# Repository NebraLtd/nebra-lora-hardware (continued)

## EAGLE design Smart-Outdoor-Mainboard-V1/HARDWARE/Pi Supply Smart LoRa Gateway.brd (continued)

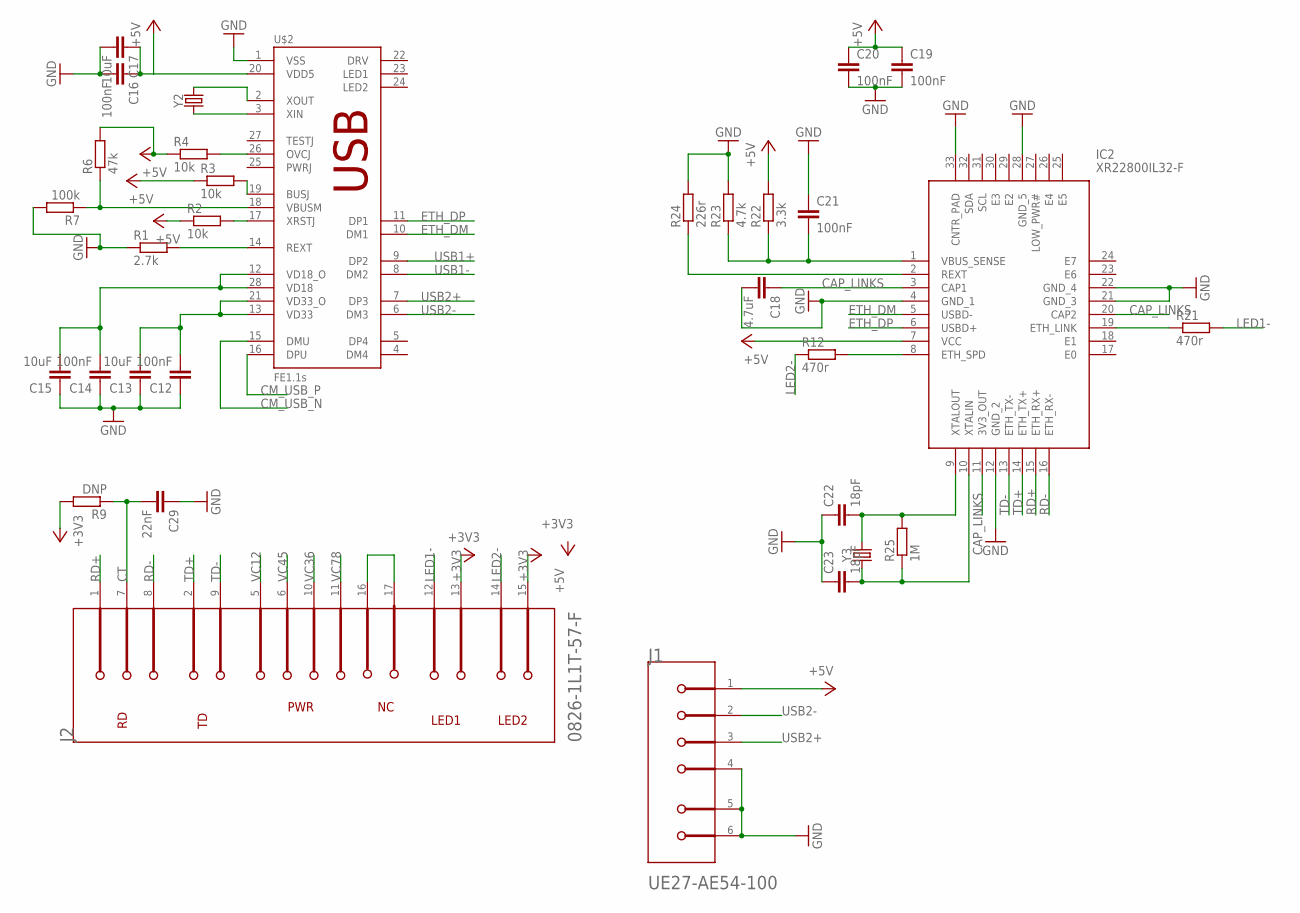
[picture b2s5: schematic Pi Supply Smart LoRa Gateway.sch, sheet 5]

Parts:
C12, C14, C16, C19, C20, C21: 100nF; C0603
C13, C15, C17: 10uF; C0603
C18: 4.7uF; C0603
C22, C23: 18pF; C0603
C29: 22nF; C0603
IC2: XR22800IL32-F; QFN50P500X500X100-33N
J1: AMPHENOL_UE27-AE54-100AMPHENOL_UE27-AE54-100_0_0; AMPHENOL_UE27-AE54-100_0
J2: TRJK1014A8NL; BEL_0826-1L1T-57-F_0
R1: 2.7k; R0603
R2, R3, R4: 10k; R0603
R6: 47k; R0603
R7: 100k; R0603
R9: DNP; R0603
R12, R21: 470r; R0603
R22: 3.3k; R0603
R23: 4.7k; R0603
R24: 226r; R0603
R25: 1M; R0603
U$2: FE1.1S; FE1.1S_SSOP-28
Y2: 12mHZ; HC49UP
Y3: 25Mhz; HC49UP

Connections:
+3V3: J2.13 (2_LED1), J2.15 (LED2_ANODE), R9.2; also elsewhere on the board
+5V: C16.1, C17.1, C19.1, C20.1, IC2.7 (VCC), J1.1, R2.1, R3.1, R4.1, R6.2, R22.2, U$2.20 (VDD5); also elsewhere on the board
CAP_LINKS: C18.1, IC2.3 (CAP1), IC2.11 (3V3_OUT), IC2.20 (CAP2)
CM_USB_N: U$2.15 (DMU); also elsewhere on the board
CM_USB_P: U$2.16 (DPU); also elsewhere on the board
CT: C29.2, J2.7 (CT), R9.1
ETH_DM: IC2.5 (USBD-), U$2.10 (DM1)
ETH_DP: IC2.6 (USBD+), U$2.11 (DP1)
GND: C12.1, C13.1, C14.1, C15.1, C16.2, C17.2, C18.2, C19.2, C20.2, C21.1, C22.1, C23.1, C29.1, IC2.4 (GND_1), IC2.12 (GND_2), IC2.21 (GND_3), IC2.22 (GND_4), IC2.28 (GND_5), IC2.33 (CNTR_PAD), J1.4, J1.5 (MNT_1), J1.6 (MNT_2), R1.1, R7.2, R23.2, R24.2, U$2.1 (VSS); also elsewhere on the board
LED1-: J2.12 (1_LED1), R21.2
LED2-: J2.14 (LED2_CATHODE), R12.1
unnamed: C12.2, C13.2, U$2.13 (VD33), U$2.21 (VD33_O)
unnamed: C14.2, C15.2, U$2.12 (VD18_O), U$2.28 (VD18)
unnamed: R4.2, U$2.26 (OVCJ)
unnamed: R1.2, U$2.14 (REXT)
unnamed: R3.2, U$2.19 (BUSJ)
unnamed: R6.1, R7.1, U$2.18 (VBUSM)
unnamed: R2.2, U$2.17 (XRSTJ)
unnamed: U$2.2 (XOUT), Y2.2
unnamed: U$2.3 (XIN), Y2.1
unnamed: IC2.19 (ETH_LINK), R21.1
unnamed: C23.2, IC2.10 (XTALIN), R25.1, Y3.1
unnamed: C22.2, IC2.9 (XTALOUT), R25.2, Y3.2
unnamed: IC2.8 (ETH_SPD), R12.2
unnamed: J2.16 (1_GND), J2.17 (2_GND)
unnamed: IC2.2 (REXT), R24.1
unnamed: C21.2, IC2.1 (VBUS_SENSE), R22.1, R23.1
RD+: IC2.15 (ETH_RX+), J2.1 (RD+)
RD-: IC2.16 (ETH_RX-), J2.8 (RD-)
TD+: IC2.14 (ETH_TX+), J2.2 (TD+)
TD-: IC2.13 (ETH_TX-), J2.9 (TD-)
USB1+: U$2.9 (DP2); also elsewhere on the board
USB1-: U$2.8 (DM2); also elsewhere on the board
USB2+: J1.3, U$2.7 (DP3)
USB2-: J1.2, U$2.6 (DM3)
VC12: J2.5 (VC12); also elsewhere on the board
VC36: J2.10 (VC36); also elsewhere on the board
VC45: J2.6 (VC45); also elsewhere on the board
VC78: J2.11 (VC78); also elsewhere on the board

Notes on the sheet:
LED2
LED1
PWR
USB

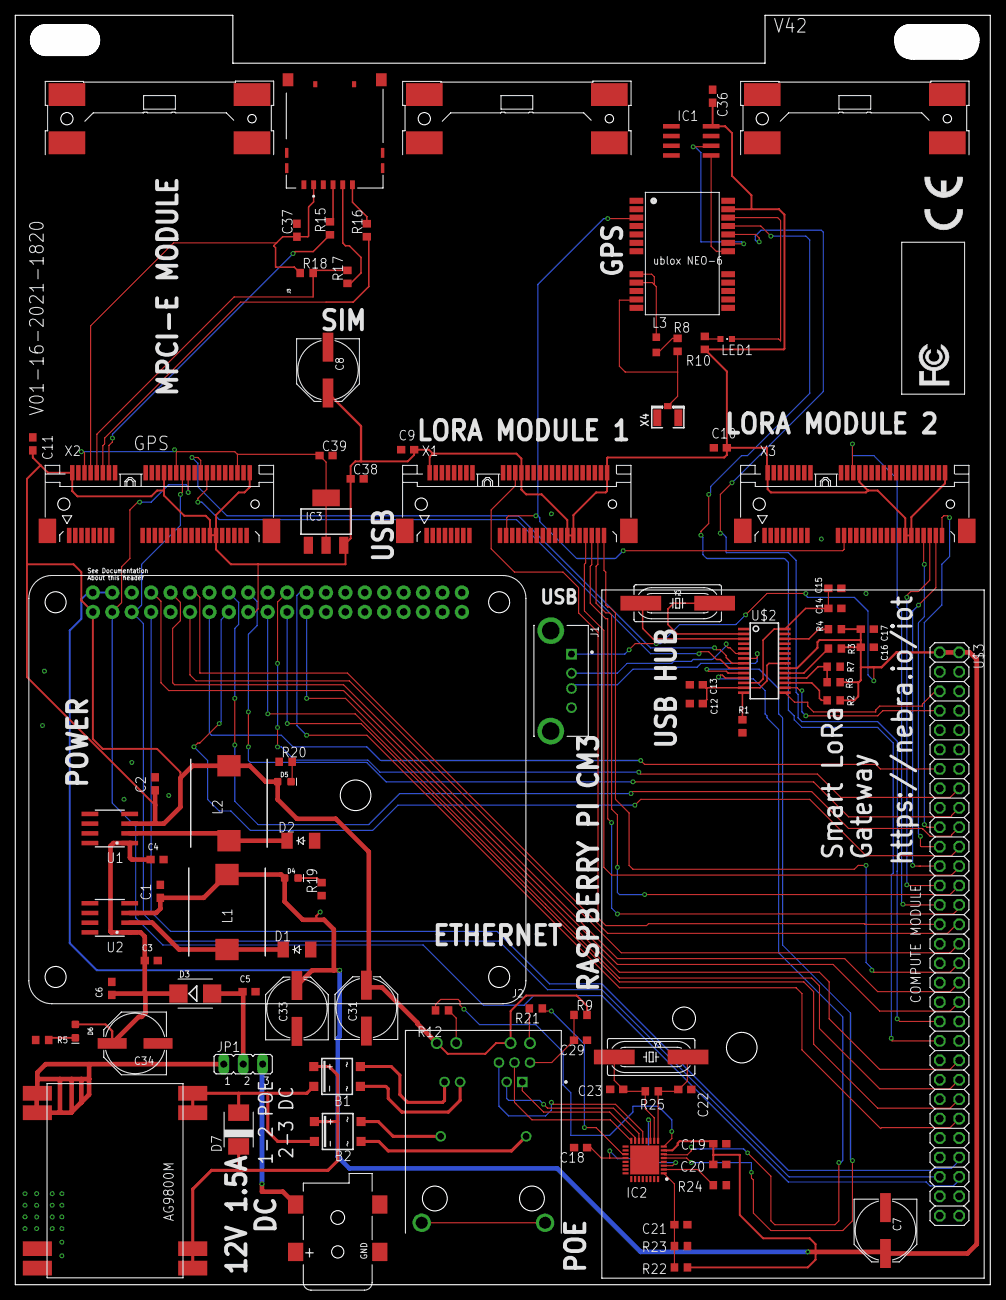
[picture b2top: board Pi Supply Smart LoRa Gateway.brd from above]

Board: 2 copper layers, 123.5 x 162.0 mm, 89 parts (0 on the bottom side), 94 nets.

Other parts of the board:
U$6: FCC_20X8.35MM
U$7: CE_5MM

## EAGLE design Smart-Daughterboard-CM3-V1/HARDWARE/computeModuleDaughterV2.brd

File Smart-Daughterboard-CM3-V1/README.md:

# Nebra Smart Daughterboard CM3
Hardware Files for the CM3 daughterboard for the Nebra Smart Hotspots

This board is used to provide the support circuitry for the CM3/CM3+, and breaks out the GPIO pins along with USB to a 60 Pin Header.

# Daughterboard Connector Pinout
The Daughterboard connector is of our own specification, it allows us in the future to create new daughterboards for other SBCs.

The electrical pinout is as follows:

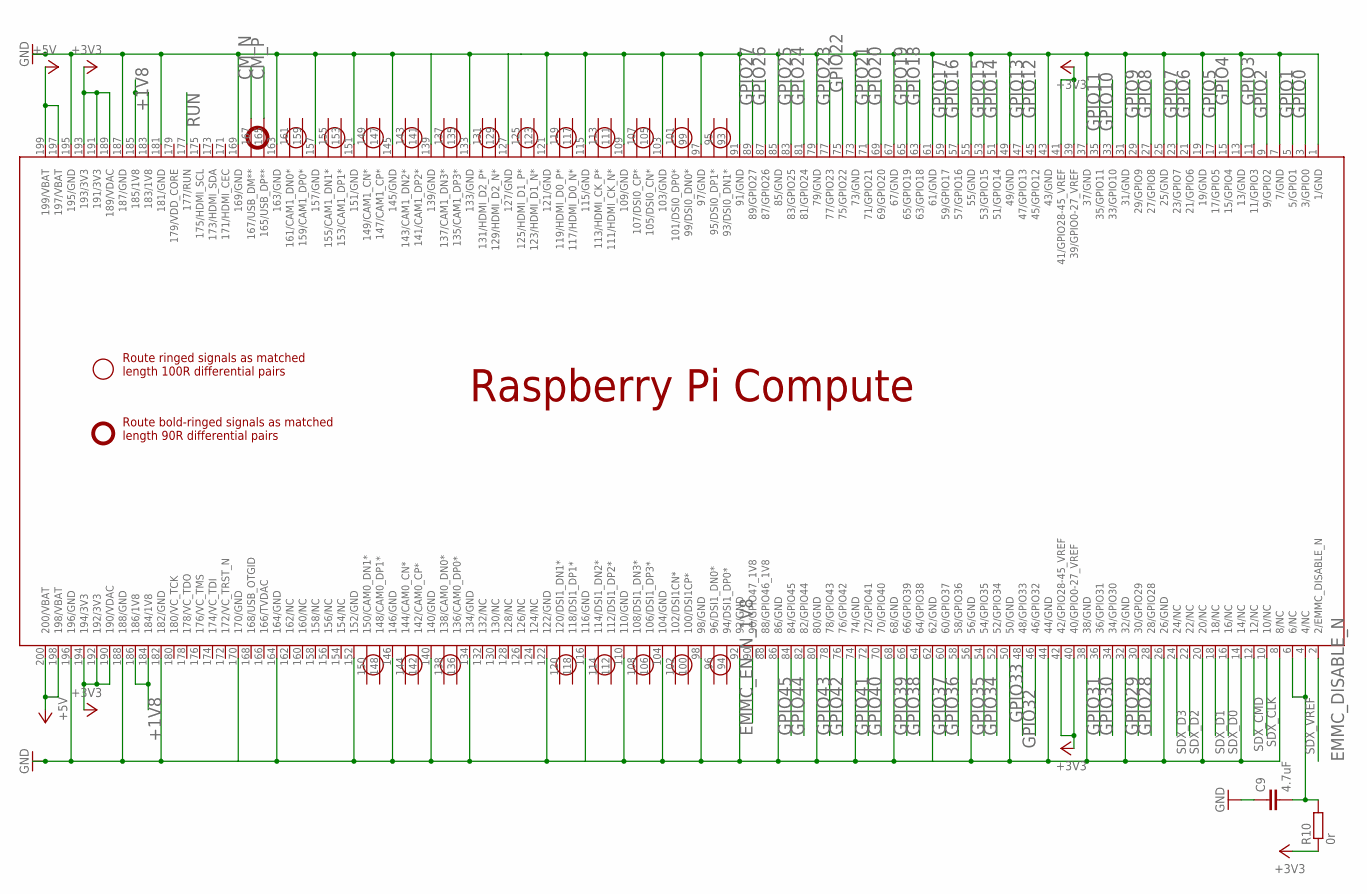
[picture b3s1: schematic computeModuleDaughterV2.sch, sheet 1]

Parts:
C9: 4.7uF; C0603
PCB1: RPI_COMPUTE
R10: 0r; R0603

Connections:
+1V8: PCB1.183 (183/1V8), PCB1.184 (184/1V8), PCB1.185 (185/1V8), PCB1.186 (186/1V8); also elsewhere on the board
+3V3: PCB1.39 (39/GPIO0-27_VREF), PCB1.40 (40/GPIO0-27_VREF), PCB1.41 (41/GPIO28-45_VREF), PCB1.42 (42/GPIO28-45_VREF), PCB1.189 (189/VDAC), PCB1.190 (190/VDAC), PCB1.191 (191/3V3), PCB1.192 (192/3V3), PCB1.193 (193/3V3), PCB1.194 (194/3V3), R10.1; also elsewhere on the board
+5V: PCB1.197 (197/VBAT), PCB1.198 (198/VBAT), PCB1.199 (199/VBAT), PCB1.200 (200/VBAT); also elsewhere on the board
CM_N: PCB1.167 (167/USB_DM**); also elsewhere on the board
CM_P: PCB1.165 (165/USB_DP**); also elsewhere on the board
EMMC_DISABLE_N: PCB1.2 (2/EMMC_DISABLE_N); also elsewhere on the board
EMMC_EN_N_1V8: PCB1.90 (90/GPIO47_1V8); also elsewhere on the board
GND: C9.1, PCB1.1 (1/GND), PCB1.7 (7/GND), PCB1.8 (8/NC), PCB1.13 (13/GND), PCB1.14 (14/NC), PCB1.19 (19/GND), PCB1.20 (20/NC), PCB1.25 (25/GND), PCB1.26 (26/GND), PCB1.31 (31/GND), PCB1.32 (32/GND), PCB1.37 (37/GND), PCB1.38 (38/GND), PCB1.43 (43/GND), PCB1.44 (44/GND), PCB1.49 (49/GND), PCB1.50 (50/GND), PCB1.55 (55/GND), PCB1.56 (56/GND), PCB1.61 (61/GND), PCB1.62 (62/GND), PCB1.67 (67/GND), PCB1.68 (68/GND), PCB1.73 (73/GND), PCB1.74 (74/GND), PCB1.79 (79/GND), PCB1.80 (80/GND), PCB1.85 (85/GND), PCB1.86 (86/GND), PCB1.91 (91/GND), PCB1.92 (92/GND), PCB1.97 (97/GND), PCB1.98 (98/GND), PCB1.103 (103/GND), PCB1.104 (104/GND), PCB1.109 (109/GND), PCB1.110 (110/GND), PCB1.115 (115/GND), PCB1.116 (116/GND), PCB1.121 (121/GND), PCB1.122 (122/GND), PCB1.127 (127/GND), PCB1.133 (133/GND), PCB1.134 (134/GND), PCB1.139 (139/GND), PCB1.140 (140/GND), PCB1.145 (145/GND), PCB1.146 (146/GND), PCB1.151 (151/GND), PCB1.152 (152/GND), PCB1.157 (157/GND), PCB1.163 (163/GND), PCB1.164 (164/GND), PCB1.169 (169/GND), PCB1.170 (170/GND), PCB1.181 (181/GND), PCB1.182 (182/GND), PCB1.187 (187/GND), PCB1.188 (188/GND), PCB1.195 (195/GND), PCB1.196 (196/GND); also elsewhere on the board
GPIO0: PCB1.3 (3/GPIO0); also elsewhere on the board
GPIO1: PCB1.5 (5/GPIO1); also elsewhere on the board
GPIO2: PCB1.9 (9/GPIO2); also elsewhere on the board
GPIO3: PCB1.11 (11/GPIO3); also elsewhere on the board
GPIO4: PCB1.15 (15/GPIO4); also elsewhere on the board
GPIO5: PCB1.17 (17/GPIO5); also elsewhere on the board
GPIO6: PCB1.21 (21/GPIO6); also elsewhere on the board
GPIO7: PCB1.23 (23/GPIO7); also elsewhere on the board
GPIO8: PCB1.27 (27/GPIO8); also elsewhere on the board
GPIO9: PCB1.29 (29/GPIO9); also elsewhere on the board
GPIO10: PCB1.33 (33/GPIO10); also elsewhere on the board
GPIO11: PCB1.35 (35/GPIO11); also elsewhere on the board
GPIO12: PCB1.45 (45/GPIO12); also elsewhere on the board
GPIO13: PCB1.47 (47/GPIO13); also elsewhere on the board
GPIO14: PCB1.51 (51/GPIO14); also elsewhere on the board
GPIO15: PCB1.53 (53/GPIO15); also elsewhere on the board
GPIO16: PCB1.57 (57/GPIO16); also elsewhere on the board
GPIO17: PCB1.59 (59/GPIO17); also elsewhere on the board
GPIO18: PCB1.63 (63/GPIO18); also elsewhere on the board
GPIO19: PCB1.65 (65/GPIO19); also elsewhere on the board
GPIO20: PCB1.69 (69/GPIO20); also elsewhere on the board
GPIO21: PCB1.71 (71/GPIO21); also elsewhere on the board
GPIO22: PCB1.75 (75/GPIO22); also elsewhere on the board
GPIO23: PCB1.77 (77/GPIO23); also elsewhere on the board
GPIO24: PCB1.81 (81/GPIO24); also elsewhere on the board
GPIO25: PCB1.83 (83/GPIO25); also elsewhere on the board
GPIO26: PCB1.87 (87/GPIO26); also elsewhere on the board
GPIO27: PCB1.89 (89/GPIO27); also elsewhere on the board
GPIO28: PCB1.28 (28/GPIO28); also elsewhere on the board
GPIO29: PCB1.30 (30/GPIO29); also elsewhere on the board
GPIO30: PCB1.34 (34/GPIO30); also elsewhere on the board
GPIO31: PCB1.36 (36/GPIO31); also elsewhere on the board
GPIO32: PCB1.46 (46/GPIO32); also elsewhere on the board
GPIO33: PCB1.48 (48/GPIO33); also elsewhere on the board
GPIO34: PCB1.52 (52/GPIO34); also elsewhere on the board
GPIO35: PCB1.54 (54/GPIO35); also elsewhere on the board
GPIO36: PCB1.58 (58/GPIO36); also elsewhere on the board
GPIO37: PCB1.60 (60/GPIO37); also elsewhere on the board
GPIO38: PCB1.64 (64/GPIO38); also elsewhere on the board
GPIO39: PCB1.66 (66/GPIO39); also elsewhere on the board
GPIO40: PCB1.70 (70/GPIO40); also elsewhere on the board
GPIO41: PCB1.72 (72/GPIO41); also elsewhere on the board
GPIO42: PCB1.76 (76/GPIO42); also elsewhere on the board
GPIO43: PCB1.78 (78/GPIO43); also elsewhere on the board
GPIO44: PCB1.82 (82/GPIO44); also elsewhere on the board
GPIO45: PCB1.84 (84/GPIO45); also elsewhere on the board
RUN: PCB1.177 (177/RUN); also elsewhere on the board
SDX_CLK: PCB1.10 (10/NC); also elsewhere on the board
SDX_CMD: PCB1.12 (12/NC); also elsewhere on the board
SDX_D0: PCB1.16 (16/NC); also elsewhere on the board
SDX_D1: PCB1.18 (18/NC); also elsewhere on the board
SDX_D2: PCB1.22 (22/NC); also elsewhere on the board
SDX_D3: PCB1.24 (24/NC); also elsewhere on the board
SDX_VREF: C9.2, PCB1.4 (4/NC), PCB1.6 (6/NC), R10.2

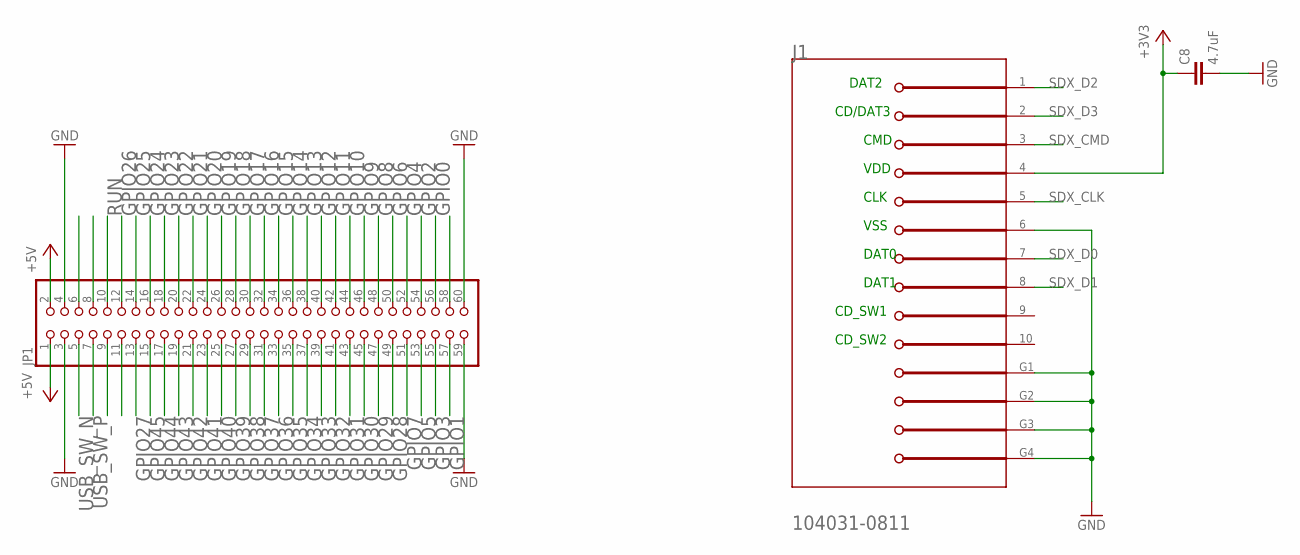
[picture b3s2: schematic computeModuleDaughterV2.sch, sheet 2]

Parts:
C8: 4.7uF; C0603
J1: MOLEX_104031-0811MOLEX_104031-0811_0_0; MOLEX_104031-0811_0
JP1: PINHD-2X30; 2X30

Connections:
+3V3: C8.1, J1.4 (VDD); also elsewhere on the board
+5V: JP1.1, JP1.2; also elsewhere on the board
GND: C8.2, J1.6 (VSS), J1.G1, J1.G2, J1.G3, J1.G4, JP1.3, JP1.4, JP1.59, JP1.60; also elsewhere on the board
GPIO0: JP1.58; also elsewhere on the board
GPIO1: JP1.57; also elsewhere on the board
GPIO2: JP1.56; also elsewhere on the board
GPIO3: JP1.55; also elsewhere on the board
GPIO4: JP1.54; also elsewhere on the board
GPIO5: JP1.53; also elsewhere on the board
GPIO6: JP1.52; also elsewhere on the board
GPIO7: JP1.51; also elsewhere on the board
GPIO8: JP1.50; also elsewhere on the board
GPIO9: JP1.48; also elsewhere on the board
GPIO10: JP1.46; also elsewhere on the board
GPIO11: JP1.44; also elsewhere on the board
GPIO12: JP1.42; also elsewhere on the board
GPIO13: JP1.40; also elsewhere on the board
GPIO14: JP1.38; also elsewhere on the board
GPIO15: JP1.36; also elsewhere on the board
GPIO16: JP1.34; also elsewhere on the board
GPIO17: JP1.32; also elsewhere on the board
GPIO18: JP1.30; also elsewhere on the board
GPIO19: JP1.28; also elsewhere on the board
GPIO20: JP1.26; also elsewhere on the board
GPIO21: JP1.24; also elsewhere on the board
GPIO22: JP1.22; also elsewhere on the board
GPIO23: JP1.20; also elsewhere on the board
GPIO24: JP1.18; also elsewhere on the board
GPIO25: JP1.16; also elsewhere on the board
GPIO26: JP1.14; also elsewhere on the board
GPIO27: JP1.13; also elsewhere on the board
GPIO28: JP1.49; also elsewhere on the board
GPIO29: JP1.47; also elsewhere on the board
GPIO30: JP1.45; also elsewhere on the board
GPIO31: JP1.43; also elsewhere on the board
GPIO32: JP1.41; also elsewhere on the board
GPIO33: JP1.39; also elsewhere on the board
GPIO34: JP1.37; also elsewhere on the board
GPIO35: JP1.35; also elsewhere on the board
GPIO36: JP1.33; also elsewhere on the board
GPIO37: JP1.31; also elsewhere on the board
GPIO38: JP1.29; also elsewhere on the board
GPIO39: JP1.27; also elsewhere on the board
GPIO40: JP1.25; also elsewhere on the board
GPIO41: JP1.23; also elsewhere on the board
GPIO42: JP1.21; also elsewhere on the board
GPIO43: JP1.19; also elsewhere on the board
GPIO44: JP1.17; also elsewhere on the board
GPIO45: JP1.15; also elsewhere on the board
RUN: JP1.12; also elsewhere on the board
SDX_CLK: J1.5 (CLK); also elsewhere on the board
SDX_CMD: J1.3 (CMD); also elsewhere on the board
SDX_D0: J1.7 (DAT0); also elsewhere on the board
SDX_D1: J1.8 (DAT1); also elsewhere on the board
SDX_D2: J1.1 (DAT2); also elsewhere on the board
SDX_D3: J1.2 (CD/DAT3); also elsewhere on the board
USB_SW_N: JP1.5; also elsewhere on the board
USB_SW_P: JP1.7; also elsewhere on the board

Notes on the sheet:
DAT2
CD/DAT3
CMD
VDD
CLK
VSS
DAT0
DAT1
CD_SW1
CD_SW2

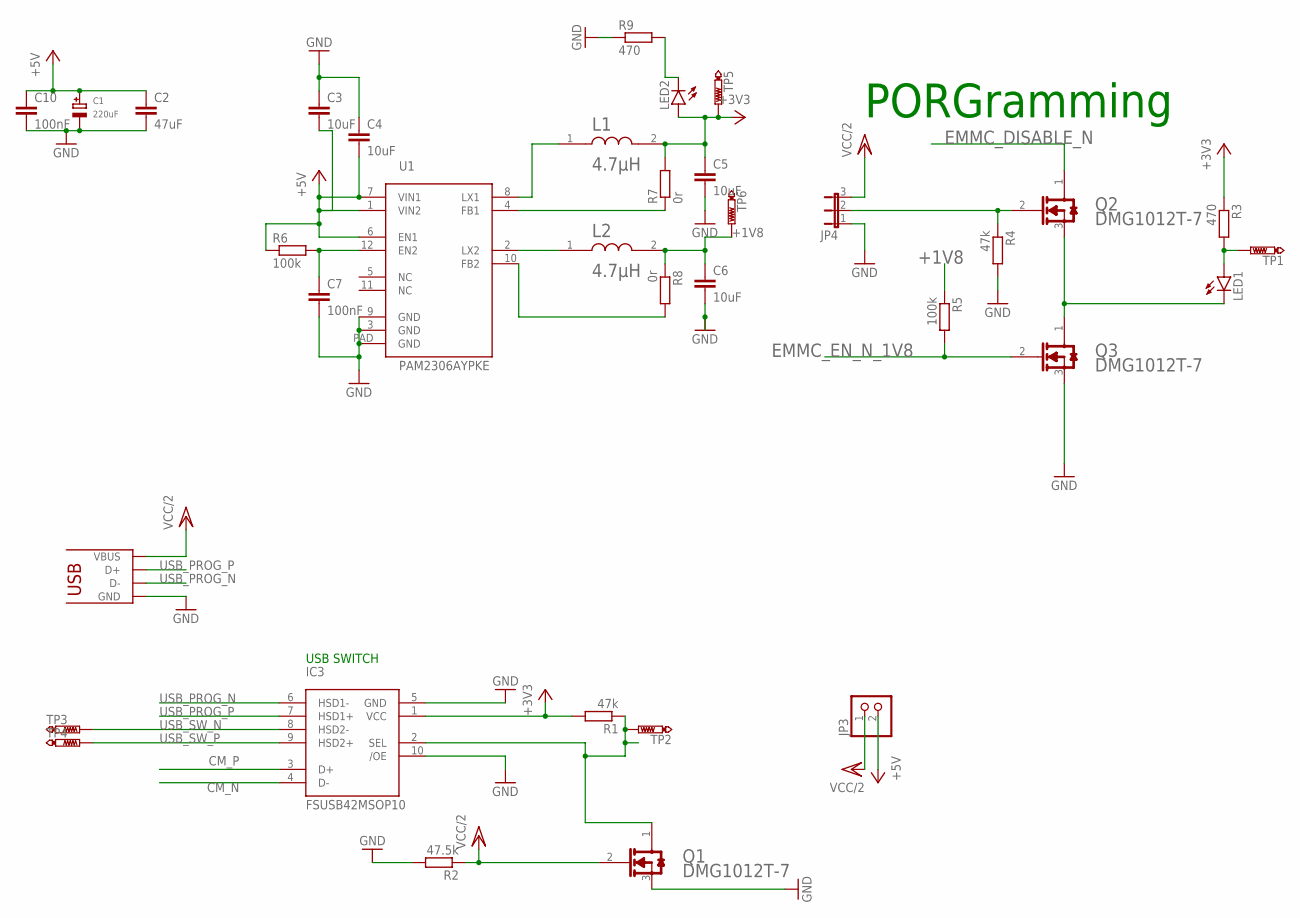
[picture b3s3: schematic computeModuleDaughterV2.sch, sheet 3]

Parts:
C1: 220uF; PANASONIC_D
C2: 47uF; C1206
C3, C4, C5, C6: 10uF; C0805
C7, C10: 100nF; C0603
IC3: FSUSB42MSOP10; MSOP10
JP2: USB-MICROB
JP3: PINHD-1X2; 1X02
JP4: JP2E; JP2
L1, L2: BOURNS_SRN4018-4R7MBOURNS_SRN4018-4R7M_0_0; BOURNS_SRN4018-4R7M_0
LED1, LED2: LEDCHIP-LED0603; CHIP-LED0603
Q1, Q2, Q3: DIODES_DMG1012T-7DIODES_DMG1012T-7_0_0; DIODES_DMG1012T-7_0
R1, R4: 47k; R0603
R2: 47.5k; R0603
R3, R9: 470; R0603
R5, R6: 100k; R0603
R7, R8: 0r; R0603
TP1, TP2, TP3, TP4, TP5, TP6: PTR1B1,27; B1,27
U1: PAM2306AYPKE; WDFN-12L

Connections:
+1V8: C6.1, L2.2, R5.1, R8.1, TP6.TP; also elsewhere on the board
+3V3: C5.1, IC3.1 (VCC), L1.2, LED2.A, R1.2, R3.1, R7.2, TP5.TP; also elsewhere on the board
+5V: C1.+, C2.1, C3.2, C4.2, C10.1, JP3.2, R6.1, U1.1 (VIN2), U1.6 (EN1), U1.7 (VIN1); also elsewhere on the board
CM_N: IC3.4 (D-); also elsewhere on the board
CM_P: IC3.3 (D+); also elsewhere on the board
EMMC_DISABLE_N: Q2.1 (DRAIN); also elsewhere on the board
EMMC_EN_N_1V8: Q3.2 (GATE), R5.2; also elsewhere on the board
GND: C1.-, C2.2, C3.1, C4.1, C5.2, C6.2, C7.2, C10.2, IC3.5 (GND), IC3.10 (/OE), JP2.GND, JP2.MT1 (GND), JP2.MT2 (GND), JP2.P$1 (GND), JP2.P$2 (GND), JP2.P$3 (GND), JP2.P$4 (GND), JP4.1, Q1.3 (SOURCE), Q3.3 (SOURCE), R2.2, R4.2, R9.1, U1.3 (GND), U1.9 (GND), U1.PAD (GND); also elsewhere on the board
unnamed: L1.1, U1.8 (LX1)
unnamed: JP4.2, Q2.2 (GATE), R4.1
unnamed: C7.1, R6.2, U1.12 (EN2)
unnamed: LED1.C, Q2.3 (SOURCE), Q3.1 (DRAIN)
unnamed: LED1.A, R3.2, TP1.TP
unnamed: L2.1, U1.2 (LX2)
unnamed: R7.1, U1.4 (FB1)
unnamed: IC3.2 (SEL), Q1.1 (DRAIN), R1.1, TP2.TP
unnamed: LED2.C, R9.2
unnamed: R8.2, U1.10 (FB2)
USB_PROG_N: IC3.6 (HSD1-), JP2.D-
USB_PROG_P: IC3.7 (HSD1+), JP2.D+
USB_SW_N: IC3.8 (HSD2-), TP3.TP; also elsewhere on the board
USB_SW_P: IC3.9 (HSD2+), TP4.TP; also elsewhere on the board
VCC/2: JP2.VBUS, JP3.1, JP4.3, Q1.2 (GATE), R2.1

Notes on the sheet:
USB SWITCH
PORGramming

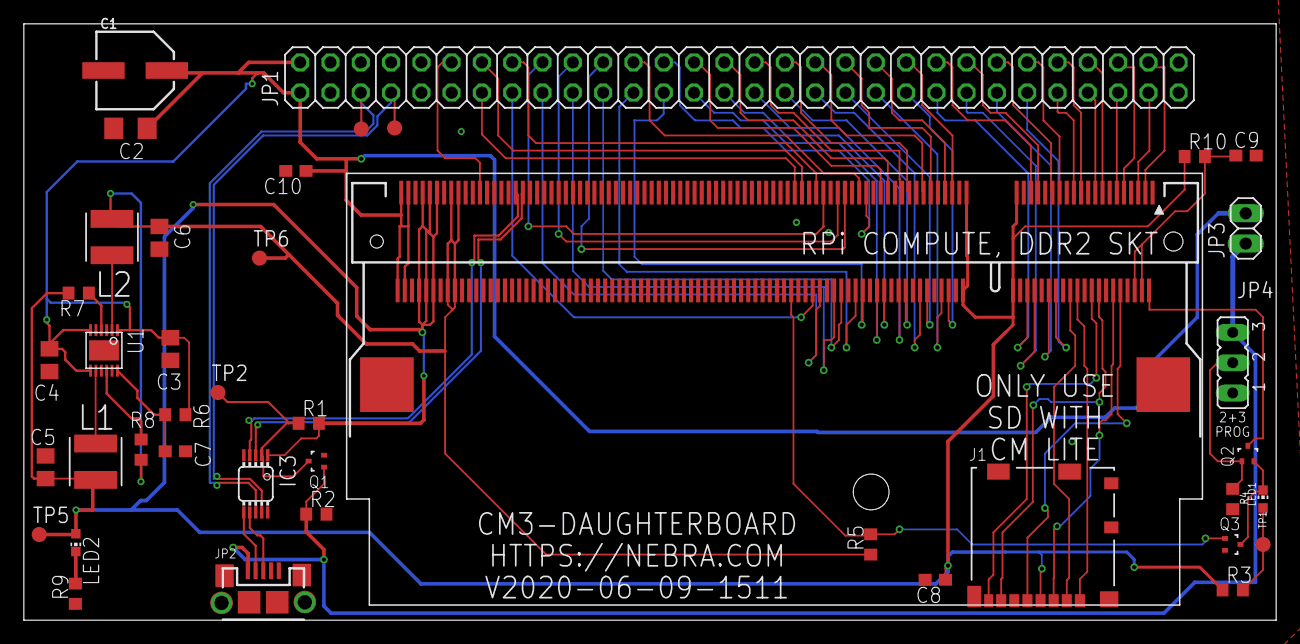
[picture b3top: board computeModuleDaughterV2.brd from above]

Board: 2 copper layers, 105.0 x 50.0 mm, 41 parts (0 on the bottom side), 77 nets.

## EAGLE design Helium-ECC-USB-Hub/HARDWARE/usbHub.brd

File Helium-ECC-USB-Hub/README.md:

# Helium ECC USB Hub
Sub Module for the Helium ECC Key combo USB Hub used on the outdoor mainboard.

This board contains space for the ATECC key used for helium hotspots, and combines in a USB Hub to provide ports for the USB & BT Adaptors on the Nebra Outdoor Hotspot.

It also has an onboard LED and Button to make BTLE pairing easier for the user.

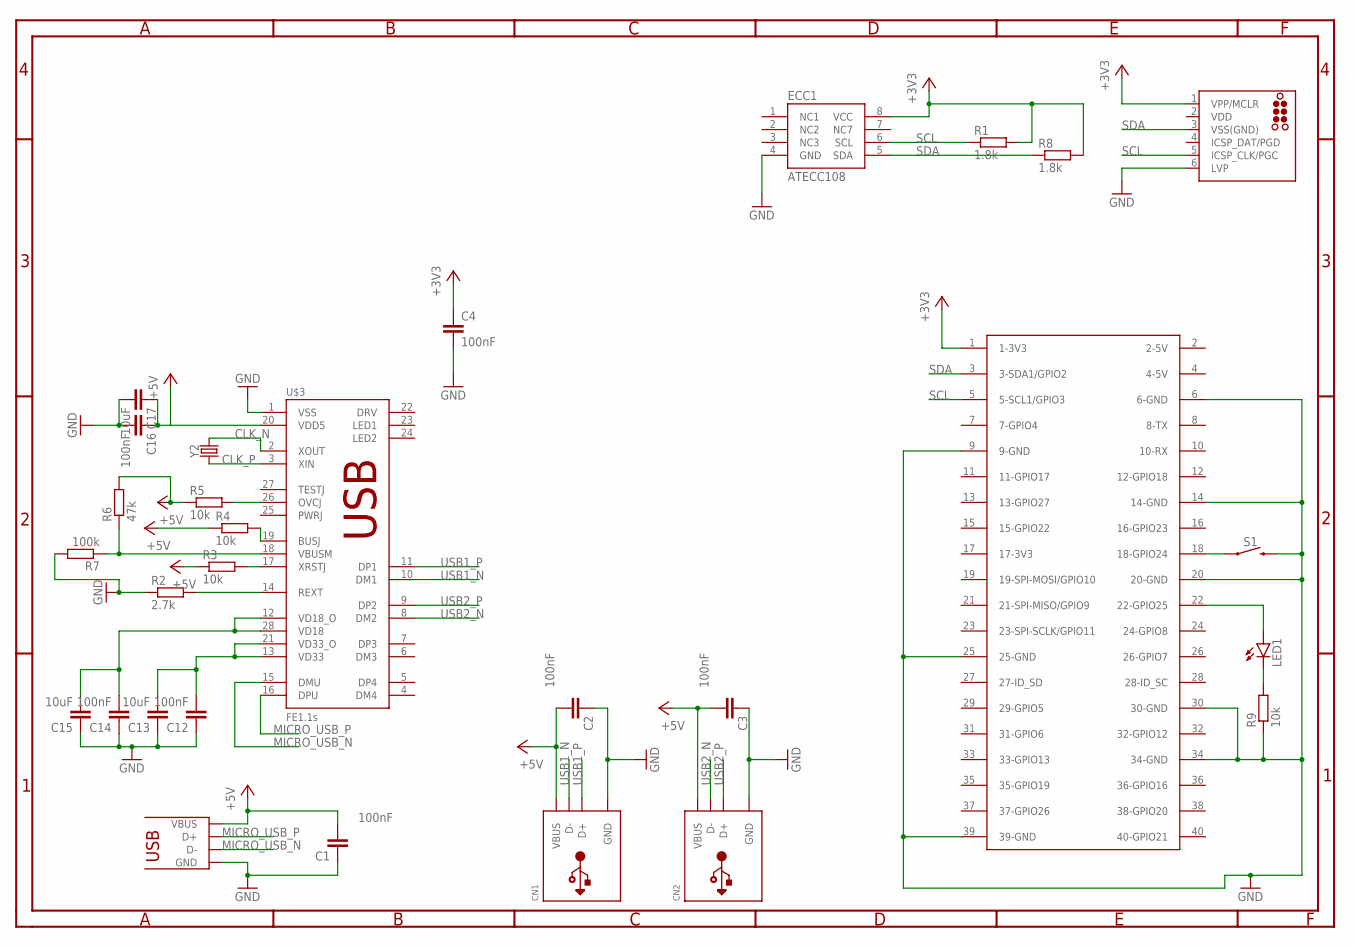
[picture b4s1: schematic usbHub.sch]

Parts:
C1, C2, C3, C4, C12, C14, C16: 100nF; C0603
C13, C15, C17: 10uF; C0603
CN1, CN2: USB_TYPEAPTHFML; USB_HOST-PTH
ECC1: ATECC108; SO08
J1: TC2030-MCP-NL
LED1: LEDCHIPLED_0603; CHIPLED_0603
R1, R8: 1.8k; R0603
R2: 2.7k; R0603
R3, R4, R5, R9: 10k; R0603
R6: 47k; R0603
R7: 100k; R0603
S1: MOMENTARY-SWITCH-SPST-SMD-6.2MM-TALL; TACTILE_SWITCH_SMD_6.2MM_TALL
U$1: USB-MICROB
U$3: FE1.1S; FE1.1S_SSOP-28
U$4: RASPBERRY-PI+HEADERONLY; RASPBERRY-PI-PLUS-HEADERONLY
Y2: 12mHZ; HC49UP

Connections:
+3V3: C4.1, ECC1.8 (VCC), J1.1 (VPP/MCLR), R1.2, R8.2, U$4.1 (1-3V3)
+5V: C1.2, C2.2, C3.2, C16.1, C17.1, CN1.VBUS, CN2.VBUS, R3.1, R4.1, R5.1, R6.2, U$1.VBUS, U$3.20 (VDD5)
CLK_N: U$3.2 (XOUT), Y2.2
CLK_P: U$3.3 (XIN), Y2.1
GND: C1.1, C2.1, C3.1, C4.2, C12.1, C13.1, C14.1, C15.1, C16.2, C17.2, CN1.GND, CN2.GND, ECC1.4 (GND), J1.6 (LVP), R2.1, R7.2, R9.1, S1.B2 (2), U$1.GND, U$1.MT1 (GND), U$1.MT2 (GND), U$1.P$1 (GND), U$1.P$2 (GND), U$1.P$3 (GND), U$1.P$4 (GND), U$3.1 (VSS), U$4.6 (6-GND), U$4.9 (9-GND), U$4.14 (14-GND), U$4.20 (20-GND), U$4.25 (25-GND), U$4.30 (30-GND), U$4.34 (34-GND), U$4.39 (39-GND)
MICRO_USB_N: U$1.D-, U$3.15 (DMU)
MICRO_USB_P: U$1.D+, U$3.16 (DPU)
unnamed: LED1.A, U$4.22 (22-GPIO25)
unnamed: S1.A2 (1), U$4.18 (18-GPIO24)
unnamed: LED1.C, R9.2
unnamed: C12.2, C13.2, U$3.13 (VD33), U$3.21 (VD33_O)
unnamed: C14.2, C15.2, U$3.12 (VD18_O), U$3.28 (VD18)
unnamed: R5.2, U$3.26 (OVCJ)
unnamed: R2.2, U$3.14 (REXT)
unnamed: R4.2, U$3.19 (BUSJ)
unnamed: R6.1, R7.1, U$3.18 (VBUSM)
unnamed: R3.2, U$3.17 (XRSTJ)
SCL: ECC1.6 (SCL), J1.5 (ICSP_CLK/PGC), R1.1, U$4.5 (5-SCL1/GPIO3)
SDA: ECC1.5 (SDA), J1.3 (VSS(GND)), R8.1, U$4.3 (3-SDA1/GPIO2)
USB1_N: CN1.D-, U$3.10 (DM1)
USB1_P: CN1.D+, U$3.11 (DP1)
USB2_N: CN2.D-, U$3.8 (DM2)
USB2_P: CN2.D+, U$3.9 (DP2)
VDD: J1.2 (VDD)

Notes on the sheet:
USB

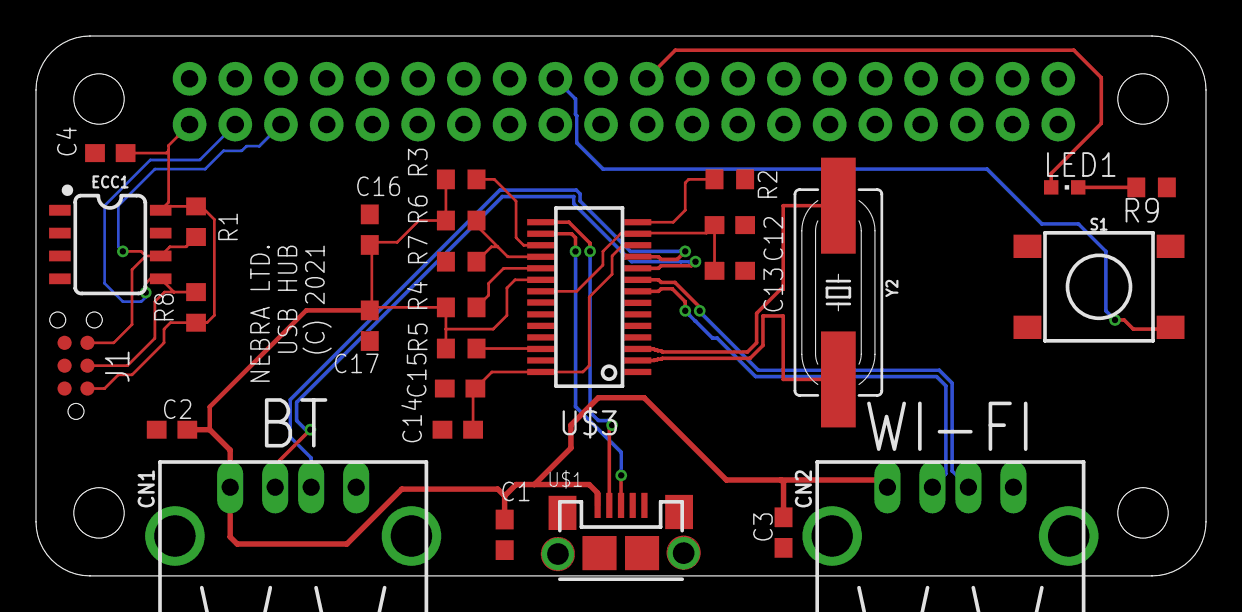
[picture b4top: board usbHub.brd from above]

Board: 2 copper layers, 65.0 x 30.0 mm, 29 parts (0 on the bottom side), 23 nets.

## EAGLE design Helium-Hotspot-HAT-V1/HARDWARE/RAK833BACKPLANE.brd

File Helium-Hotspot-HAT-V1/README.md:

# Nebra Helium Hotspot Hat

The Nebra Helium Hotspot HAT is designed for the new generation of Nebra Helium Hotspots.

It features space for the Radio Module, a button & two LEDs. Along with an EEPROM to store RPi HAT data and a ATECC to comply with Helium Hotspot Requirements.

# DIY Note

Please note, while you are able to build a DIY option of this board it will not earn HNT unless the ECC is programmed by an authorised Helium Maker.

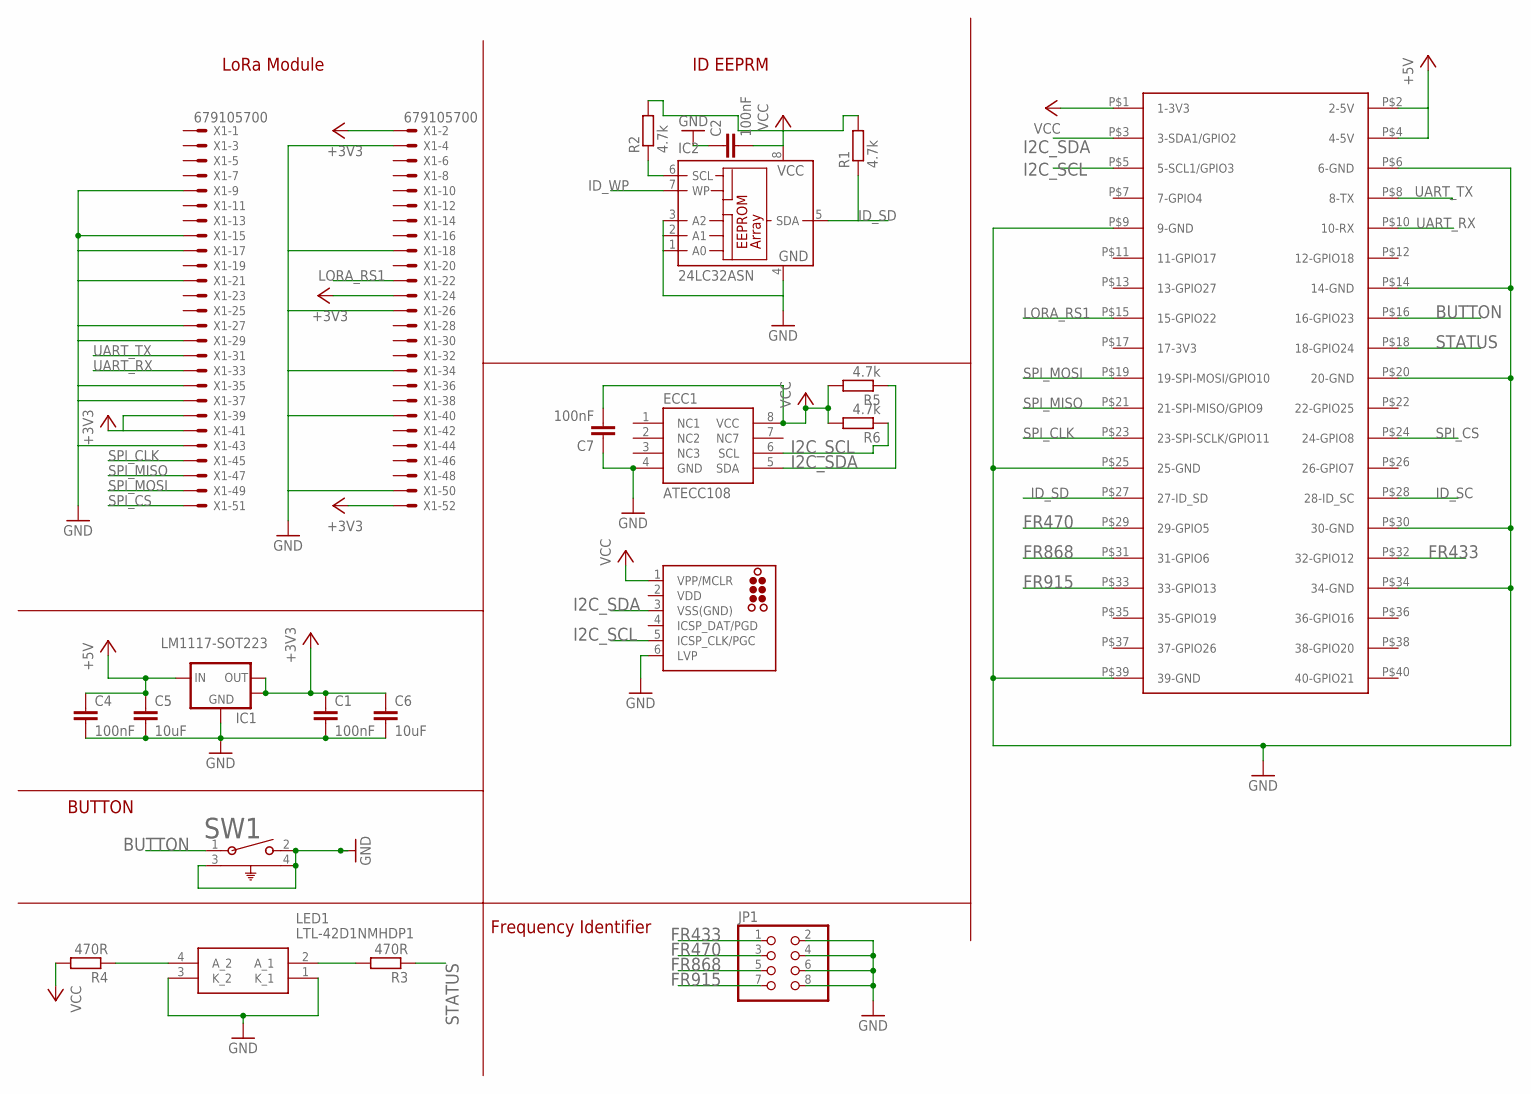
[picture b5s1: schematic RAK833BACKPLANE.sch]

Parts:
C1, C2, C4, C7: 100nF; C0402
C5, C6: 10uF; C0603
ECC1: ATECC108; SO08
IC1: LM1117-SOT223; SOT-223-3
IC2: 24LC32ASN; SO-08
J1: TC2030-MCP-NL
JP1: PINHD-2X4; 2X04
LED1: LTL-42D1NMHDP1; LTL42D1NMHDP1
R1, R2, R5, R6: 4.7k; R0402
R3, R4: 470R; R0402
SW1: 1825027-8; SW2_1825027-C_TEC
U$2: RASPBERRY-PI+; RASPBERRY-PI-PLUS-CAM_NOTCH
X1: 679105700

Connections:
+3V3: C1.1, C6.1, IC1.2 (VOUT), IC1.4 (HEATSINK), X1.2, X1.24, X1.39, X1.41, X1.52
+5V: C4.1, C5.1, IC1.3 (VIN), U$2.P$2 (2-5V), U$2.P$4 (4-5V)
BUTTON: SW1.1, U$2.P$16 (16-GPIO23)
FR433: JP1.1, U$2.P$32 (32-GPIO12)
FR470: JP1.3, U$2.P$29 (29-GPIO5)
FR868: JP1.5, U$2.P$31 (31-GPIO6)
FR915: JP1.7, U$2.P$33 (33-GPIO13)
GND: C1.2, C2.1, C4.2, C5.2, C6.2, C7.1, ECC1.4 (GND), IC1.1 (GND), IC2.1 (A0), IC2.2 (A1), IC2.3 (A2), IC2.4 (GND), J1.6 (LVP), JP1.2, JP1.4, JP1.6, JP1.8, LED1.1 (K_1), LED1.3 (K_2), SW1.2, SW1.3, SW1.4, U$2.P$6 (6-GND), U$2.P$9 (9-GND), U$2.P$14 (14-GND), U$2.P$20 (20-GND), U$2.P$25 (25-GND), U$2.P$30 (30-GND), U$2.P$34 (34-GND), U$2.P$39 (39-GND), X1.4, X1.9, X1.15, X1.17, X1.21, X1.26, X1.27, X1.29, X1.34, X1.35, X1.37, X1.40, X1.43, X1.50
I2C_SCL: ECC1.6 (SCL), J1.5 (ICSP_CLK/PGC), R6.1, U$2.P$5 (5-SCL1/GPIO3)
I2C_SDA: ECC1.5 (SDA), J1.3 (VSS(GND)), R5.1, U$2.P$3 (3-SDA1/GPIO2)
ID_SC: IC2.6 (SCL), R2.1, U$2.P$28 (28-ID_SC)
ID_SD: IC2.5 (SDA), R1.1, U$2.P$27 (27-ID_SD)
ID_WP: IC2.7 (WP)
LORA_RS1: U$2.P$15 (15-GPIO22), X1.22
unnamed: LED1.4 (A_2), R4.1
unnamed: LED1.2 (A_1), R3.2
SPI_CLK: U$2.P$23 (23-SPI-SCLK/GPIO11), X1.45
SPI_CS: U$2.P$24 (24-GPIO8), X1.51
SPI_MISO: U$2.P$21 (21-SPI-MISO/GPIO9), X1.47
SPI_MOSI: U$2.P$19 (19-SPI-MOSI/GPIO10), X1.49
STATUS: R3.1, U$2.P$18 (18-GPIO24)
UART_RX: U$2.P$10 (10-RX), X1.33
UART_TX: U$2.P$8 (8-TX), X1.31
VCC: C2.2, C7.2, ECC1.8 (VCC), IC2.8 (VCC), J1.1 (VPP/MCLR), R1.2, R2.2, R4.2, R5.2, R6.2, U$2.P$1 (1-3V3)
VDD: J1.2 (VDD)

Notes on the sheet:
LoRa Module
BUTTON
ID EEPRM
Frequency Identifier
